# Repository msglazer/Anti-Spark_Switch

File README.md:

# Anti Spark Switch
Personal improvements/changes to the vedder antispark switch

Design allows for a battery to be connected to a source without the usual spark in the connector, also provides a convenient on off ability.
Improvements to the design include an upgraded, more robust fuse and fuse holder, an additional MOSFET for higher current handling as well as
better distribution of power through the MOSFETs. There is also the option of adding an LED powered through the PCB, the LED is powered after the MOSFET switch

There are two versions currently, with fuse and without fuse. The without fuse version is located in its own branch, master contains the fuse version

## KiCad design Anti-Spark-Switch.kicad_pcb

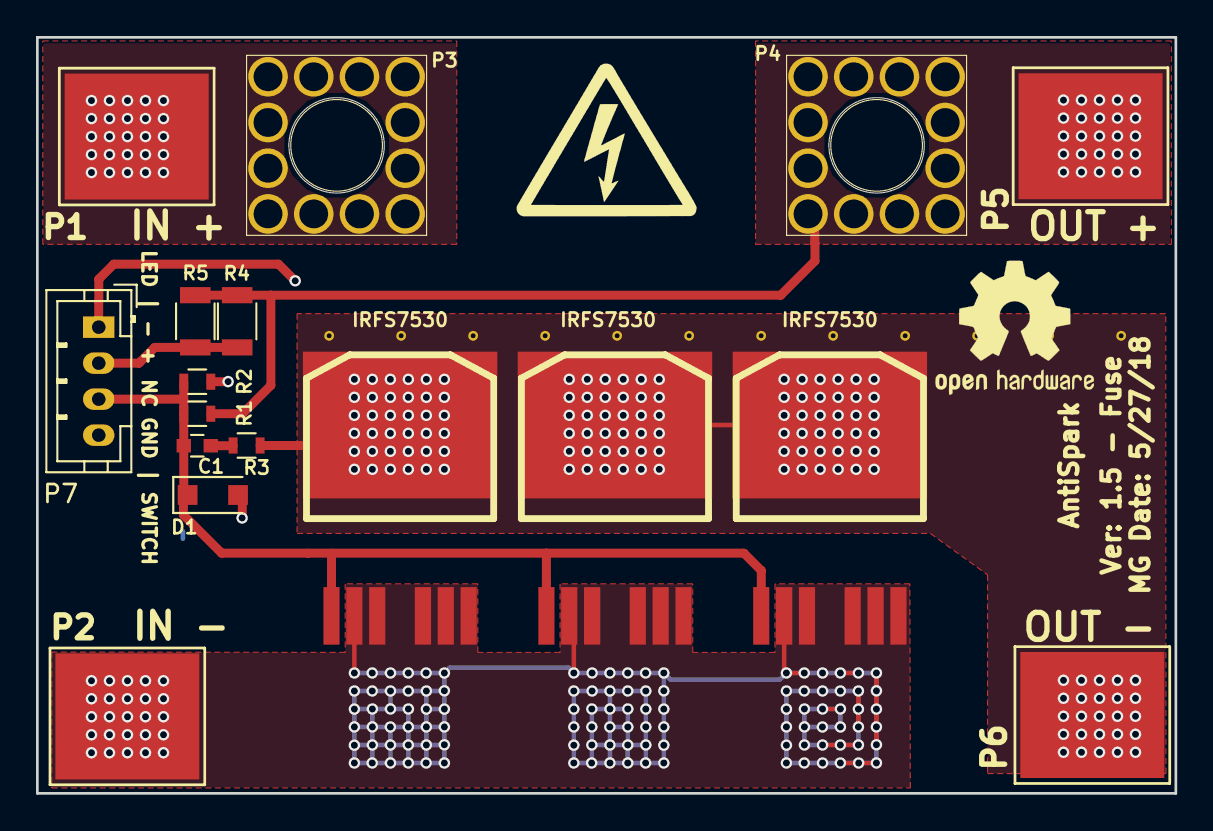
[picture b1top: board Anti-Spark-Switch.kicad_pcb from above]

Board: 2 copper layers, 63.2 x 42.0 mm, 17 parts (0 on the bottom side), 7 nets.

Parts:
C1: 1uF; C_0603
D1: ZENER; D_SOD-123F
P1, P2, P5, P6: Pad_Conn; 1PAD_8x7mm
P3, P4: Screw_Terminal; M5_Screw_Terminal_12_pin
P7: CONN_01X04; JST_PH_B4B-PH-K_1x04_P2.00mm_Vertical
Q1, Q2, Q3: IRFS7530; D2PAK-7-GDS
R1, R2: 1M; R_0603
R3: 1K; R_0603
R4, R5: 16.5K; R_1206

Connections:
/SW_NC: C1.2, D1.1, P7.3, Q1.G, Q2.G, Q3.G, R1.2, R2.1
GND: D1.2, P2.1, P7.4, Q1.S, Q2.S, Q3.S, R2.2
unnamed: C1.1, R3.2
unnamed: P4.1, P5.1, R1.1, R4.1, R5.1
unnamed: P6.1, P7.1, Q1.D, Q2.D, Q3.D, R3.1
unnamed: P7.2, R4.2, R5.2
VCC: P1.1, P3.1

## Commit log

2016-07-01 :tada: Added .gitattributes & .gitignore files
2016-07-01 initial commit, schematic 90% done
2016-07-07 schematic completed, PCB started
2016-07-08 continued work on PCB
2016-07-13 finalized rev 1 PCB, generated gerbers, captured images
2016-07-15 updated BOM, shifted schematic
2016-07-19 gerber update
2016-08-10 changed fuse value
2016-09-20 Rev 1.1 changes
    Moved Gate power input from before to after fuse for improved safety
2016-09-23 Text changes to schematic
2016-09-23 minor Rev 1.1 changes
2016-09-23 text fixes/passive component footprint changes
2016-09-23 added some images
2016-09-23 updated gerbers
2016-09-23 BOM update
2016-09-23 updated a footprint, fixed reference numbers
2016-09-23 slight change to through hole diameter
2017-02-12 Fixed short through LED issue
    may still need some tweaking
2018-04-19 updated schematic, changed bom slightly
2018-04-19 moved images to new folder, updated a PCB footprint
2018-04-21 fixed component
2018-04-21 V1.3 Gerbers
2018-04-21 updated the PCB per new schematic changes and general improvements
2018-04-21 schematic changes and updating the netlist
2018-04-21 potential drill issue
2018-04-21 updated the gerber zip file
2018-05-19 updated gerber files
2018-05-19 current version schematic pdf
2018-05-19 changed connector to JST-PH-4 vertical connector, added silkscreen stuff
2018-05-19 fixed silkscreen issue
2018-05-20 Generated new gerbers for no fuse and fixed file names
2018-05-20 added picture of PCB
2018-05-20 removed fuse, changed board size, tweaked layout
2018-05-20 Fixed file name
2018-05-20 improved the PCB a bit
2018-05-20 added an image
2018-05-27 updated the gerbers
2018-05-27 making sure the zip file is up to date
2018-05-27 PCB has been updated per a fixed screw terminal component
2018-05-27 updated the gerbers, change is V1.5 now
